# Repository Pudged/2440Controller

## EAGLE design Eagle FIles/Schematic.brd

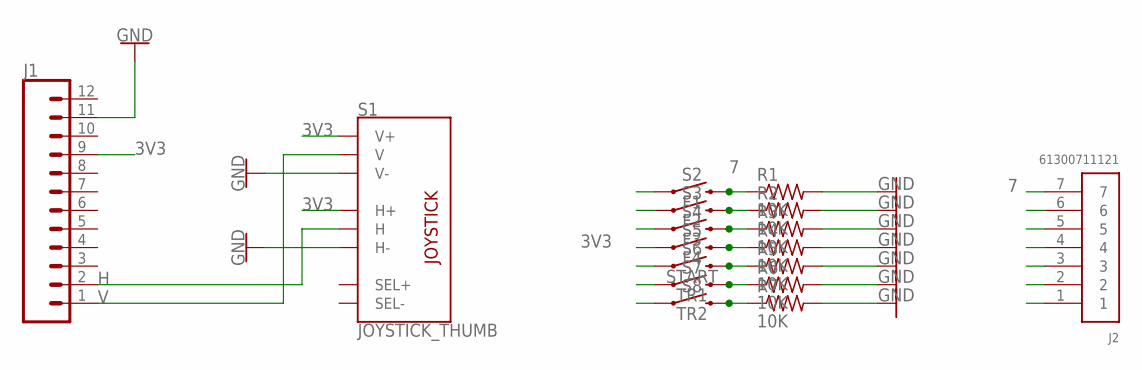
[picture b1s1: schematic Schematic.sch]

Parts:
J1: CONN_12NO_SILK; 1X12_NO_SILK
J2: 61300711121
R1, R2, R3, R4, R5, R6, R7: 10K; RES_1206
S1: JOYSTICK_THUMB; JOYSTICK
S2: F1; TACTILE_SWITCH_PTH_12MM
S3: F2; TACTILE_SWITCH_PTH_12MM
S4: F3; TACTILE_SWITCH_PTH_12MM
S5: F4; TACTILE_SWITCH_PTH_12MM
S6: START; TACTILE_SWITCH_PTH_12MM
S7: TR1; TACTILE_SWITCH_PTH_RIGHT_ANGLE_KIT
S8: TR2; TACTILE_SWITCH_PTH_RIGHT_ANGLE_KIT

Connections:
1: J2.1, R7.1, S8.2
2: J2.2, R6.1, S7.2
3: J2.3, R5.1, S6.3 (2)
3V3: J1.9, S1.H1 (H+), S1.V1 (V+), S2.1, S3.1, S4.1, S5.1, S6.1, S7.1, S8.1
4: J2.4, R4.1, S5.3 (2)
5: J2.5, R3.1, S4.3 (2)
6: J2.6, R2.1, S3.3 (2)
7: J2.7, R1.1, S2.3 (2)
GND: J1.11, R1.2, R2.2, R3.2, R4.2, R5.2, R6.2, R7.2, S1.H3 (H-), S1.V3 (V-)
H: J1.2, S1.H2 (H)
V: J1.1, S1.V2 (V)

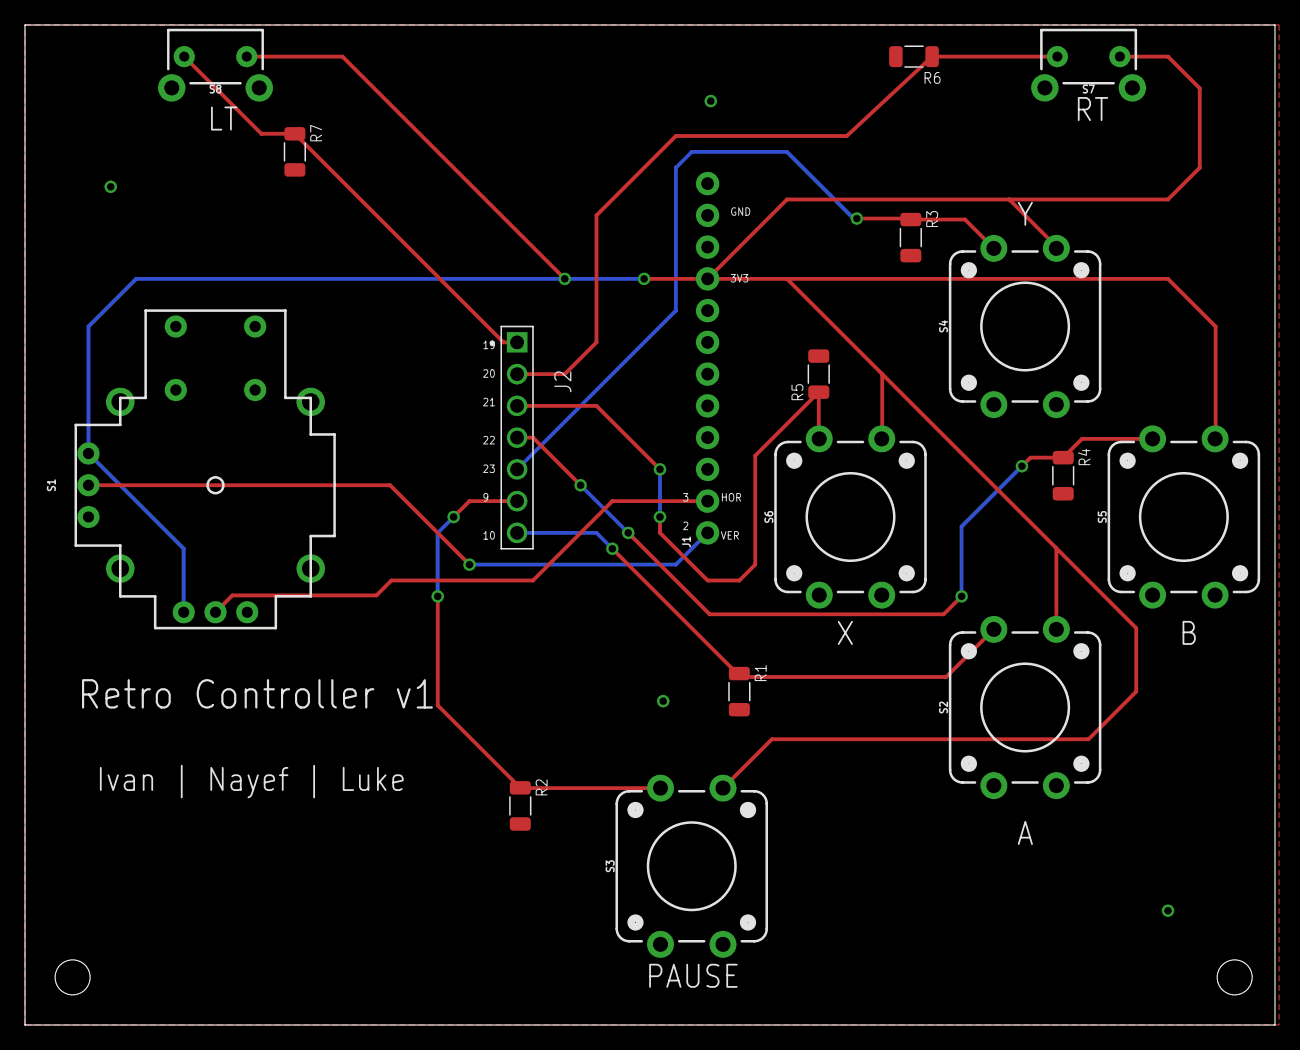
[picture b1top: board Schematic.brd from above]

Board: 2 copper layers, 100.0 x 80.0 mm, 17 parts (0 on the bottom side), 11 nets.

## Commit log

2020-04-29 Buttons Done
2020-05-05 Added UART for buttons
2020-05-05 README updated

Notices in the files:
parts and their libraries:
SparkFun-Connectors: Licensing: Creative Commons ShareAlike 4.0 International - https://creativecommons.org/licenses/by-sa/4.0
